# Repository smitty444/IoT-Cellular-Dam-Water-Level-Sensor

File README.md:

# IOT-Cellular-Dam-Water-Level-Sensor
This is an Arduino Mega based stage sensor developed by interns at the South Carolina Department of Health and Environmental Control (SC DHEC) Dam Safety Program. The purpose of this sensor is to provide a low-cost, open-source alternative to traditional gaging equipment. Both an ultrasonic sensor and a pressure transducer are used to measure stage, and all data is sent via the Hologram cellular network to a graphic user interface (GUI) hosted on Adafruit IO. *Note: this repository was formerly named "DHEC-Stage-Sensor".

<p align="center">
Figure 1: Sensor deployed on the primary spillway of a dam transmitting data to the GUI.
</p>

## characteristic data
contains validation data for the sensor, as well as test data for filtering, pressure transducer calibration

## code
contains all the Arduino code for the sensor

## EDA
contains all electronic design automation (EDA) files for the custom datalogging and power PCBs

## field tests
contains data for all field tests performed with the sensor package, as well as Python scripts for visualizing data

# Citation
Cite as:

@Misc{Smith2022DHECStageSensor,     
  author = {Corinne Smith and Parker Lovett and John McCain and Austin Downey},  
  howpublished = {GitHub},  
  title  = {DHEC Stage Sensor},
  year   = {2022},  
  groups = {ARTS-Lab},    
  url    = {https://github.com/ARTS-Laboratory/IoT-Cellular-Dam-Water-Level-Sensor },   
}

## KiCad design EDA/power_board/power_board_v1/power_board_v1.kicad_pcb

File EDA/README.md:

## Overview
1. All PCBs were designed running KiCAD 6.0
2. Custom schematic symbols are located in lib_and_pretty\ARTS-Lab.lib
3. Custom footprint symbols are located in lib_and_pretty\dhec.pretty

## Datalogger PCB
The datalogger PCB is the main data acquisition and saving board. It contains the DS3231 real-time clock, microSD card module, MPRLS ambient pressure sensor, JSN-SR04 ultrasonic sensor, pressure transducer port, and indicator LEDs. 

<p align="center">
Figure 1: Datalogger board showing a) the PCB layout and the 3D rendering of the PCB b) front and c) back.
</p>

## Power control PCB
The power control PCB is used to monitor the package battery voltage and regulate the voltage to 5V for powering the Arduino Mega. It contains the INA219 current sensor and a barrel battery connector. 

<p align="center">
Figure 1: Power control board showing a) the PCB layout and the 3D rendering of the PCB b) front and c) back.
</p>

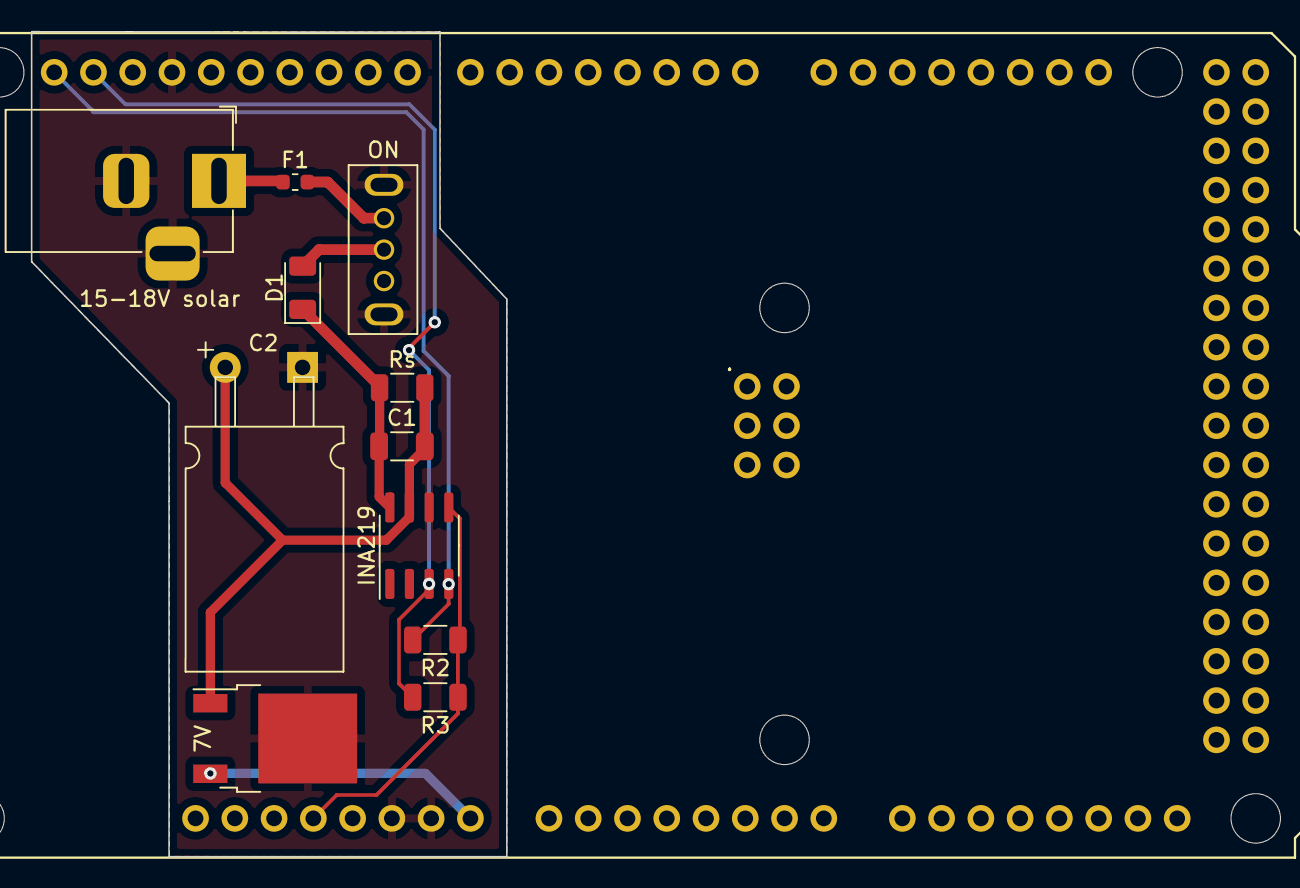
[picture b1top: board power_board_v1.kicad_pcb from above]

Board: 2 copper layers, 30.7 x 53.4 mm, 12 parts (0 on the bottom side), 10 nets.

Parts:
7V: LF15_TO252; TO-252-2
15-18V solar: Barrel_Jack; BarrelJack_Horizontal
C1: C; C_1206_3216Metric
C2: C; CP_Radial_D10.0mm_P5.00mm_L16.00mm_bent
D1: D; D_1206_3216Metric
F1: Fuse; Fuse_0603_1608Metric
INA219: INA219AxD; SOIC-8_3.9x4.9mm_P1.27mm
ON: grounded_DIP_switch; grounded_switch
R2, R3: 4.7k; R_1206_3216Metric
Rs: shunt; R_1206_3216Metric
XA1: Arduino_Mega2560_Shield

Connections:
GND: 7V.2 (GND), 15-18V solar.2, 15-18V solar.3, C2.2, INA219.6 (GND), ON.4, ON.5, XA1.GND1 (GND), XA1.GND2 (GND), XA1.GND3 (GND)
unnamed: C1.1, D1.1 (K), INA219.8 (IN+), Rs.1
unnamed: 7V.1 (VI), C1.2, C2.1, INA219.7 (IN-), Rs.2
unnamed: D1.2 (A), ON.2
unnamed: 15-18V solar.1, F1.1
unnamed: F1.2, ON.1
unnamed: INA219.5 (VS), R2.1, R3.1, XA1.3V3 (3.3V)
unnamed: INA219.4 (SCL), R2.2, XA1.SCL
unnamed: INA219.3 (SDA), R3.2, XA1.SDA
unnamed: 7V.3 (VO), XA1.VIN

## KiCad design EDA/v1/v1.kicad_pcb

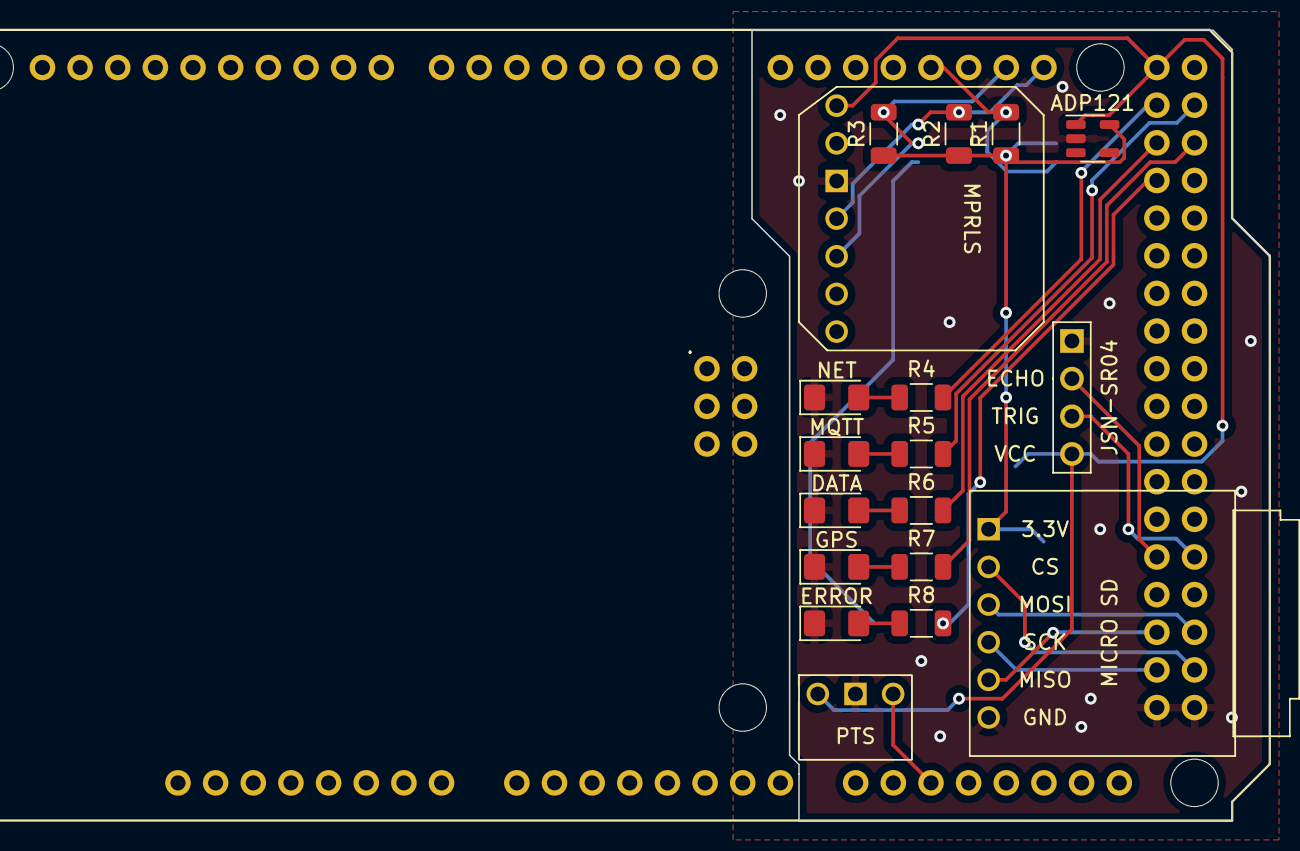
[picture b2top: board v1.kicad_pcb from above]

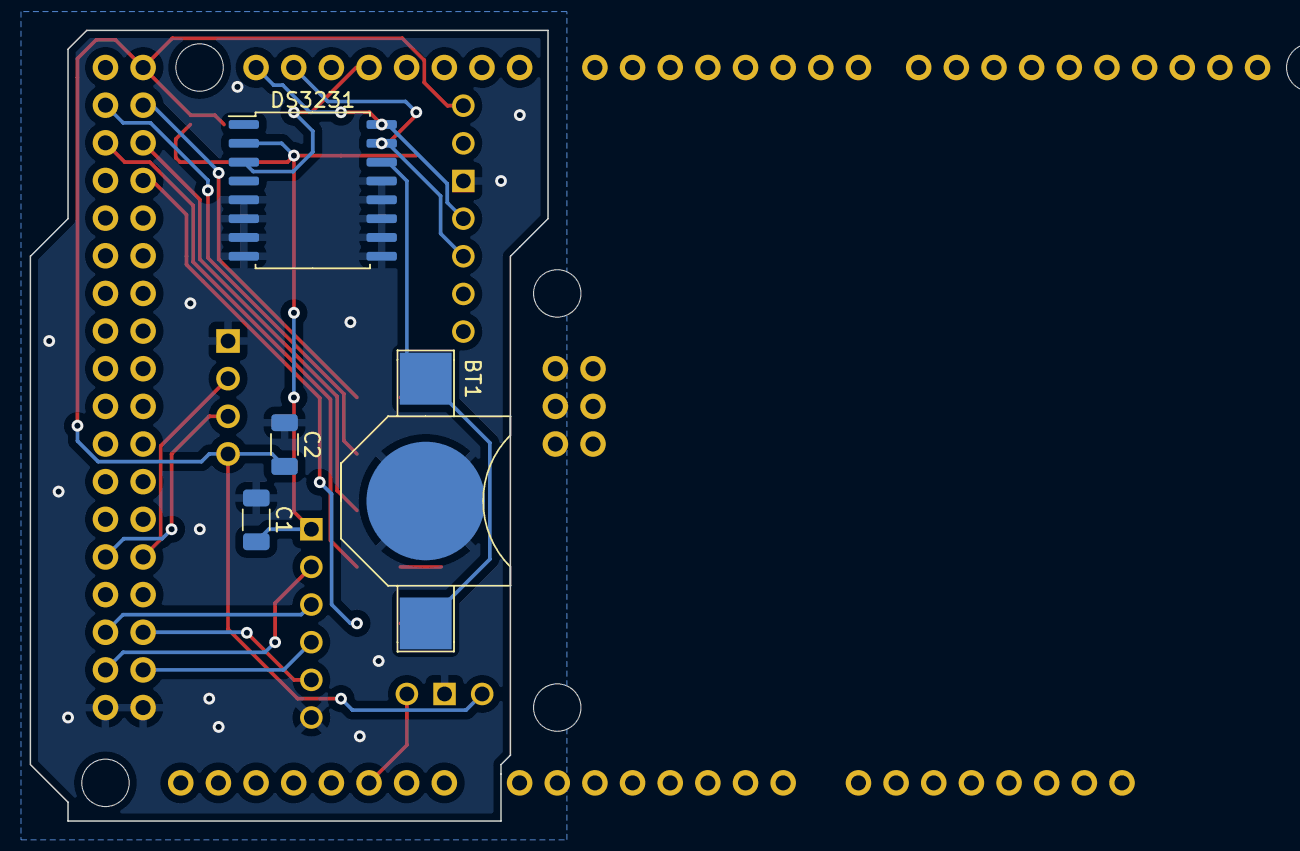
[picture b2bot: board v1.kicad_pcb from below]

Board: 2 copper layers, 34.9 x 53.3 mm, 23 parts (4 on the bottom side), 24 nets.

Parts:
ADP121: TC2014-3.3VxCTTR; SOT-23-5
BT1: Battery_Cell; battery_holder_10mm
C1, C2: C; C_1206_3216Metric
DATA: LED; LED_1206_3216Metric_Pad1.42x1.75mm_HandSolder
DS3231: DS3231M; SOIC-16W_7.5x10.3mm_P1.27mm
ERROR: LED; LED_1206_3216Metric_Pad1.42x1.75mm_HandSolder
GPS: LED; LED_1206_3216Metric_Pad1.42x1.75mm_HandSolder
JSN-SR04: HCSR04
MICRO SD: microSD_small; small_microSD_v2
MPRLS: MPRLS
MQTT: LED; LED_1206_3216Metric_Pad1.42x1.75mm_HandSolder
NET: LED; LED_1206_3216Metric_Pad1.42x1.75mm_HandSolder
PTS: Pressure_transducer; pressure_sensor
R1, R2, R3, R4, R5, R6, R7, R8: R; R_1206_3216Metric
XA1: Arduino_Mega2560_Shield

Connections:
GND: ADP121.2 (GND), BT1.2 (-), C1.1, C2.1, DATA.1 (K), DS3231.5 (GND), DS3231.6 (GND), DS3231.7 (GND), DS3231.8 (GND), DS3231.9 (GND), DS3231.10 (GND), DS3231.11 (GND), DS3231.12 (GND), DS3231.13 (GND), ERROR.1 (K), GPS.1 (K), JSN-SR04.1 (GND), MICRO SD.6 (GND), MPRLS.3 (GND), MQTT.1 (K), NET.1 (K), PTS.2 (GND), XA1.GND5 (GND), XA1.GND6 (GND)
unnamed: BT1.1 (+), DS3231.14 (VBAT)
unnamed: NET.2 (A), R4.2
unnamed: MQTT.2 (A), R5.2
unnamed: DATA.2 (A), R6.2
unnamed: GPS.2 (A), R7.2
unnamed: ERROR.2 (A), R8.2
unnamed: ADP121.5 (VOUT), C1.2, DS3231.2 (VCC), MICRO SD.1 (3.3V), R1.1, R2.1, R3.1
unnamed: MICRO SD.2 (CS), XA1.D53 (D53_SS)
unnamed: MICRO SD.3 (MOSI), XA1.D51
unnamed: MICRO SD.4 (CLK), XA1.D52
unnamed: MICRO SD.5 (MISO), XA1.D50
unnamed: DS3231.16 (SCL), MPRLS.4 (SCL), R2.2, XA1.D21 (D21_SCL)
unnamed: DS3231.15 (SDA), MPRLS.5 (SDA), R3.2, XA1.D20 (D20_SDA)
unnamed: R4.1, XA1.D22
unnamed: R5.1, XA1.D23
unnamed: R6.1, XA1.D24
unnamed: R7.1, XA1.D25
unnamed: R8.1, XA1.D26
unnamed: ADP121.1 (VIN), C2.2, JSN-SR04.4 (VCC), MPRLS.1 (VIN), PTS.1 (5V), XA1.5V3 (5V)
unnamed: PTS.3 (Sig), XA1.A10
unnamed: DS3231.3 (~INT/SQW), R1.2, XA1.D18 (D18_TX1)
unnamed: JSN-SR04.2 (ECHO), XA1.D46
unnamed: JSN-SR04.3 (TRIG), XA1.D47

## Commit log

2022-01-12 add test code and necessary libraries
2022-01-25 add debugging scripts
2022-01-25 add data collection scripts
2022-01-25 add flowchart
2022-01-25 update libraries
2022-01-25 stabilize deploy_switch_tester.ino
    The deployment switch works, temp, pressure, and stage are all published successfully.
2022-01-25 added WHS_v1.1.ino
    updated from v1 with deployment control loop in setup
2022-01-26 stabilize deploy_switch_tester.ino
    The deployment control and publications all work, and parameters like sea level and sampling rate can be initialized before the deployment switch is pressed. Control is in void setup.
2022-01-28 fix pressure sensor reading
2022-01-28 incorporate linear scaling equation
2022-01-31 uncomment #define MQTT_DEBUG to connect MQTT
2022-02-01 Update pressure_tester.ino
    add Serial input and a push button to control when readings are taken. Made for lab test descending_feb1.txt
2022-02-01 Create pressure_field_test.ino
    Serial input and a push button to control when readings are taken. Made for lab test descending_feb1.txt
2022-02-01 Revert "Update pressure_tester.ino"
    This reverts commit b91f9afb9aa6d315b22d7a460967bbe3e4502017.
2022-02-01 change gps failure message
2022-02-02 more debugging codes
    clock calibration and an update tester
2022-02-02 calculate average values and save to SD
2022-02-03 moving pressure data
2022-02-03 add SD card readings
2022-02-03 Create WHS_v1.2.1.ino
    Used for testing in the field, only publishes pressure and temperature data
2022-02-04 incorporate gps manual control
2022-02-07 fix location boolean control
2022-02-08 reorganizing versioning
2022-02-08 add rtc and gps power saving
2022-02-10 create v1 EDA
2022-02-10 move libraries around
2022-02-12 moving things around
2022-02-14 reorganize EDA
2022-02-14 reorganize code
2022-02-14 add pie chart
2022-02-15 create 5 min cycle pie charts
2022-02-15 add contact sensor
2022-02-22 update characteristic data
2022-02-22 allow minutes or seconds alarm units
2022-02-24 incorporate power saving techniques
    turn gps off after collection and in setup, fix logic on pulling DTR pin up and down, fix AT+CSCLK command
2022-02-25 resolve cpp.o error
2022-03-01 change pressure reading from hPa to psi
2022-03-03 add minute/second option
2022-03-08 keepalive troubleshooting
2022-03-12 add publishing delays
2022-03-15 change pins for datalogging board
2022-03-15 debugging
2022-03-16 create power board
2022-03-16 fix connectivity issues associated with low power modes, add delay to go into sleep mode
    AT+CSCLK=1 always, DTR is pulled LOW at all times except during sleep mode. Delays are required after pulling LOW/HIGH so that everything wakes/sleeps properly. Delay required before entering sleep m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
2022-03-16 rename whs2.0.1 (fixed with low power)
2022-03-16 add fona lipo monitor
2022-03-17 add gerber files
2022-03-17 update PCB
2022-03-18 create backups
2022-03-21 add control sequence used in WHS_v2.0.2 for debugging
2022-03-21 Update WHS_v2.0.2.ino
    include tolerances, ping calculations, remainder calculations. Remainder calculations still throwing errors
2022-03-25 add delay for ping function, initialize remainder to sampling_rate
    delay needed to avoid timeout before ping is successfully sent. remainder initialized to sampling rate to get rid of unnecessary else statement
2022-03-25 initializer remainder to sampling_rate
2022-03-30 restructuring
    new file branching off water level sensor and syphon sensor codes
2022-04-04 3/31 field test data
2022-04-04 add feeds for second package
2022-04-06 make compatible with second package
    Add whs-2 feeds, change to minutes rather than seconds for alarm, edit remainder variable to sampling_rate for continuity
2022-04-06 increase FONA wakeup delay
2022-04-06 Create WHS_v2.1.0_noSPI.ino
    an adaptive sampling script to adjust for the shorted SD card and SPI communications
2022-04-12 process field testing data
2022-04-12 add field test photos
2022-04-18 compare filter
2022-04-18 separately test filters
2022-04-20 add last replacement filter
2022-04-29 testing and visualization
2022-04-29 filtering testing and visualization
2022-04-29 add sensor 2 feeds
2022-04-29 organize comments
2022-04-29 plot 4/22 field test
2022-04-29 add voltage feeds
2022-04-29 comment sensor 1 feeds
2022-04-29 comment adaptive descriptions
2022-05-12 change variable "tolerance" to "distError"
    "tolerance" was used twice in both the median filter and RTC alarm setting
2022-05-12 data processing for may 3 - 9 deployment
2022-05-16 change distance reading threshold, integrate power feeds
2022-05-20 change readings to cm, account for diode voltage drop, change reading to F
2022-05-20 change folder names
2022-05-20 plot 5/12 - 5/17 field test data
2022-05-20 plot temperature and pressure transducer drift
2022-05-25 add DS3232 library
2022-05-25 fix pressure correction factor
2022-06-02 add may 20 - 25 field test
2022-06-09 update figure dimensions
2022-06-12 change linewidth
2022-06-12 remove post-fieldtest data
2022-06-12 change line styles
2022-06-13 add gui_and_sensor.png
2022-06-15 capitalize Kalman
2022-06-15 fix figure
2022-06-15 clean up libraries
2022-06-15 add figures
2022-06-15 add citation
2022-06-16 remove AIO credentials
2022-06-16 add backups
2022-06-28 process data
2022-06-28 fix image
2022-06-28 update citation
2022-06-29 change x axis title from "distance" to "elevation"
2022-07-01 add hobo test data
2022-07-01 add WHS2 feeds, change initial elevation from int type to float
2022-07-02 change font size
2022-07-06 add legend
2022-07-13 add figure
2022-07-13 change font to arial
2022-07-13 change line colors
2022-07-15 add power board v2
2022-07-15 add 07/01-07/15 field test
2022-07-19 rename folder
2022-07-19 change plot size, pressure transducer label
2022-07-19 remove figure files
2022-07-26 fix url
2022-08-04 backups
2022-08-12 change font to times new roman
2022-08-15 fix image path
2022-10-28 reduce font
2022-10-28 change font to tnr, change size
